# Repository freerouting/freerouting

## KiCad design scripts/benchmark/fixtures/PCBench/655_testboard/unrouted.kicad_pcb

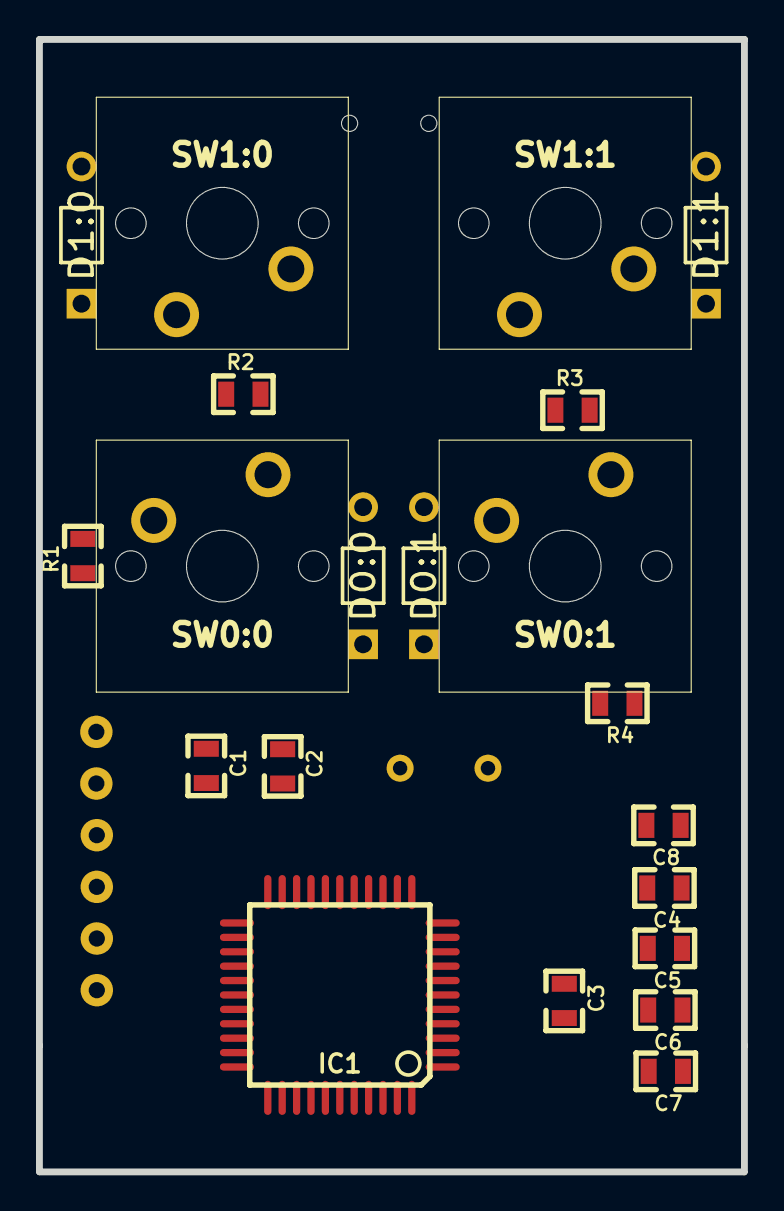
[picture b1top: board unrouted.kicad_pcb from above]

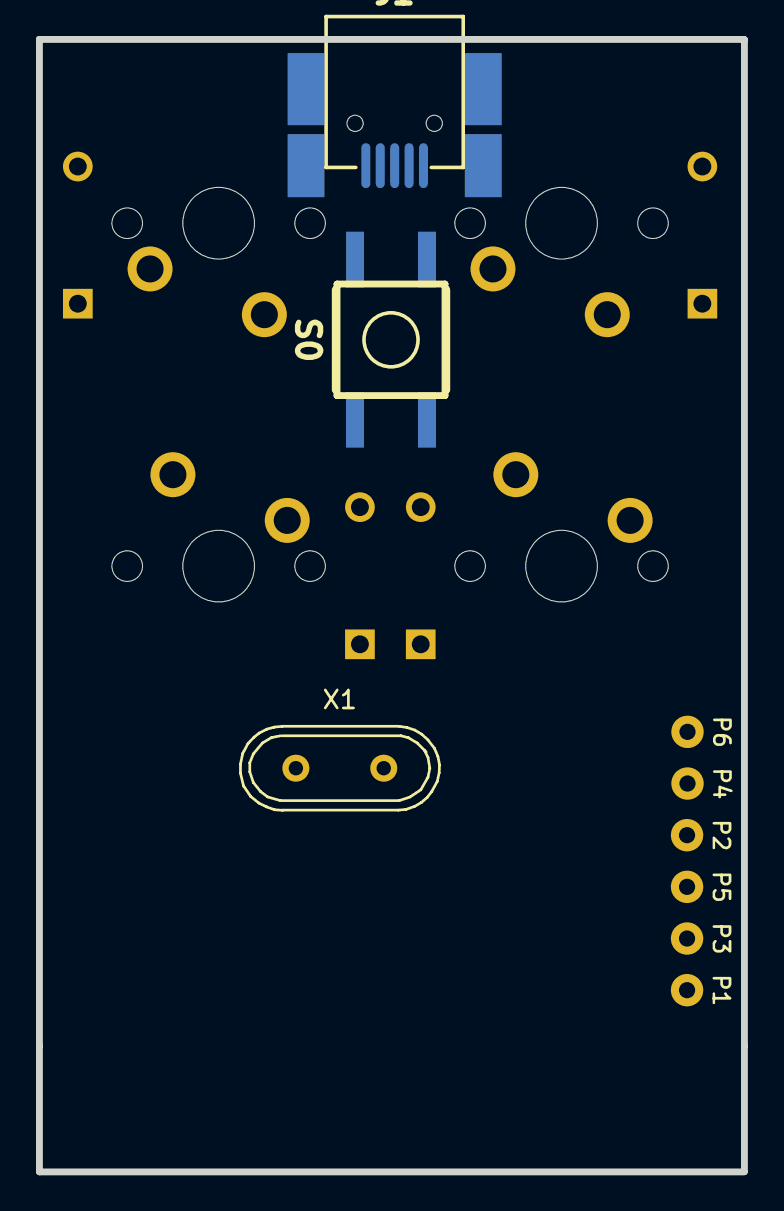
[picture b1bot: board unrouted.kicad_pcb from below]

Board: 2 copper layers, 39.2 x 62.9 mm, 30 parts (9 on the bottom side), 22 nets, no tracks yet.

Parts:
C1, C2: 22p; 0805C
C3, C8: 1u; 0805C
C4, C5, C6, C7: 100n; 0805C
D0:0, D0:1, D1:0, D1:1: D; DIODE
IC1: ATMEGA32U4; TQFP44
J1: USBMINI_B05; 67503
P1, P2, P3, P4, P5, P6: CONN_1; pad
R1, R2: 22; 0805R
R3, R4: 10k; 0805R
S0: DTSM-6; KSEM31GLFS
SW0:0: F0; MX1A
SW0:1: CTRL; MX1A
SW1:0: F1; MX1A
SW1:1: SHIFT; MX1A
X1: CRYSTAL; Crystal_HC49-U_Vertical

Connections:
/COL0: D0:0.2, D1:0.2, IC1.8
/COL1: D0:1.2, D1:1.2, IC1.41
/MISO: IC1.11, P1.1
/MOSI: IC1.10, P4.1
/RES: IC1.13, P5.1, R4.2, S0.3
/ROW0: IC1.18, SW0:0.1, SW0:1.1
/ROW1: IC1.19, SW1:0.1, SW1:1.1
/SCK: IC1.9, P3.1
GND: C1.2, C2.2, C3.2, C4.2, C5.2, C6.2, C7.2, C8.2, IC1.5, IC1.15, IC1.23, IC1.35, IC1.43, J1.5, P6.1, R3.1, S0.1
unnamed: C1.1, IC1.16, X1.1
unnamed: C2.1, IC1.17, X1.2
unnamed: C3.1, IC1.6
unnamed: D0:0.1, SW0:0.2
unnamed: D0:1.1, SW0:1.2
unnamed: D1:0.1, SW1:0.2
unnamed: D1:1.1, SW1:1.2
unnamed: IC1.3, R1.1
unnamed: IC1.4, R2.1
unnamed: IC1.33, R3.2
unnamed: J1.2, R1.2
unnamed: J1.3, R2.2
VCC: C4.1, C5.1, C6.1, C7.1, C8.1, IC1.2, IC1.7, IC1.14, IC1.24, IC1.34, IC1.44, J1.1, P2.1, R4.1

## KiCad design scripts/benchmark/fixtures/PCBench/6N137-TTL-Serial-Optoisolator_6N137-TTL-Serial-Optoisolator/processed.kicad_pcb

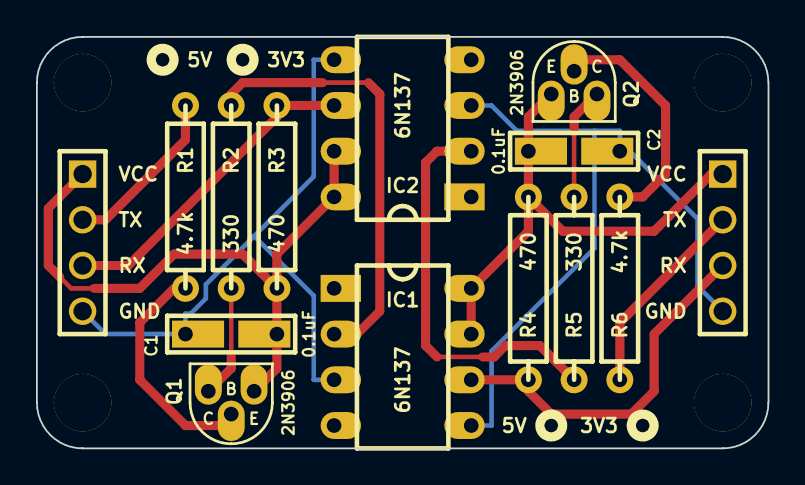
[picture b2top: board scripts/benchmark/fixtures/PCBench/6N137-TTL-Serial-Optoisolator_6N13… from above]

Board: 2 copper layers, 40.6 x 22.9 mm, 18 parts (0 on the bottom side), 14 nets.

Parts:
C1, C2: 0.1uF; CERCAP_2_059B_0805
H***: Val**; hole_M3_2
H***_2, H***_3, H***_4: Val**; hole_M3_2
IC1, IC2: 6N137; DIP8_059Bi_PL
P1, P2: CONN_4; PIN_ARRAY_4x1
Q1, Q2: 2N3906; TO-92_Q_EBC_059Bo_PL
R1, R6: 4.7k; R_AXIAL_0W25_059A_PL
R2, R5: 330; R_AXIAL_0W25_059A_PL
R3, R4: 470; R_AXIAL_0W25_059A_PL

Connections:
GNDA: C1.2, IC1.3, IC2.5, P1.4
GNDB: C2.2, IC1.5, IC2.3, P2.4
unnamed: Q2.2, R6.2
unnamed: Q1.2, R1.2
unnamed: Q1.3, R2.2
unnamed: Q2.3, R5.2
unnamed: IC1.2, R2.1
unnamed: IC2.2, R5.1
RXA: IC2.6, P1.3, R3.1
RXB: IC1.6, P2.3, R4.1
TXA: P1.2, R1.1
TXB: P2.2, R6.1
VCCA: C1.1, IC2.7, IC2.8, P1.1, Q1.1, R3.2
VCCB: C2.1, IC1.7, IC1.8, P2.1, Q2.1, R4.2

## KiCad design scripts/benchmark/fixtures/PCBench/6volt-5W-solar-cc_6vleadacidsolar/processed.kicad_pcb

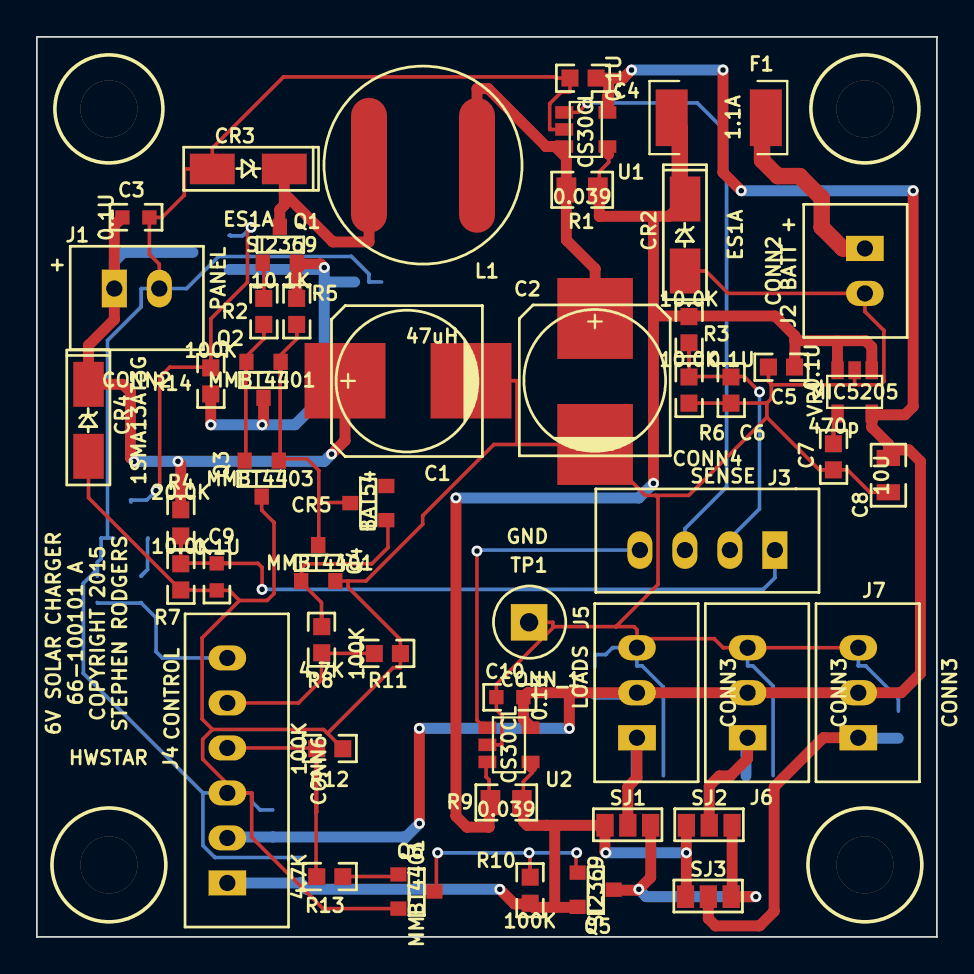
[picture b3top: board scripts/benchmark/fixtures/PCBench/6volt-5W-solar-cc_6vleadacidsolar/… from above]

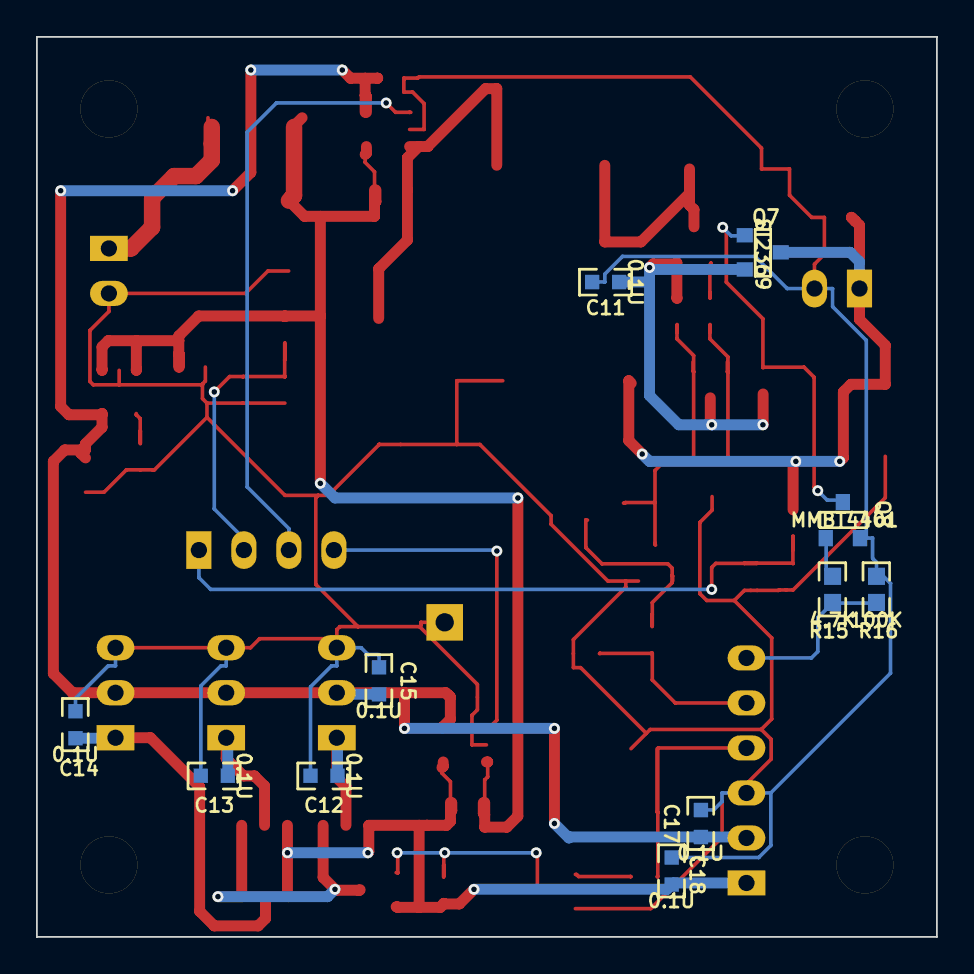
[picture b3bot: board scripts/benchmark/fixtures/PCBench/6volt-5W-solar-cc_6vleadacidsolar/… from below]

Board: 2 copper layers, 50.0 x 50.0 mm, 65 parts (11 on the bottom side), 29 nets.

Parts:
C1, C2: 470U; CAP_ELEC_SMT_8X10
C3, C9, C10, C11, C12, C13, C14, C15, C17, C18: 0.1U; CC0603
C4, C5, C6: 0.1U; RC0603
C7: 470p; RC0603
C8: 10U; CC0805
CR2, CR3: ES1A; SMA-SAR
CR4: 1SMA13AT3G; SMA-SAR
CR5: BAT54; SOT23-3-SAR
F1: 1.1A; MINISMD1812
J1, J2: CONN2; JST_B2B_XH_A
J3: CONN4; JST_B4B_XH_A
J4: CONN6; JST_B6B_XH_A
J5, J6, J7: CONN3; JST_B3B_XH_A
L1: 47uH; BOURNS-SDE0805A
MTGHOLE125, MTGHOLE125_2, MTGHOLE125_3, MTGHOLE125_4: VAL**; MTGHOLE125
Q1, Q5, Q7: SI2369; SOT23-3-SAR
Q2, Q4, Q6, Q8: MMBT4401; SOT23-3-SAR
Q3: MMBT4403; SOT23-3-SAR
R1, R9: 0.039; RC0805
R2: 10; RC0603
R3, R6, R7: 10.0K; RC0603
R4: 20.0K; RC0603
R5: 1K; RC0603
R8, R13, R15: 4.7K; RC0603
R10, R11, R12, R14, R16: 100K; RC0603
SJ1, SJ2, SJ3: GS3; SJ3
TP1: CONN_1; TESTPIN
U1, U2: CS30CL; SOT23-5-SAR
VR1: MIC5205; SOT23-5-SAR

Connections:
+5V: C4.1, C8.1, C10.1, C15.1, C17.1, J4.2, J5.2, J6.2, J7.2, U1.5, U2.5, VR1.5
+BATT: C5.1, CR2.2, F1.1, R1.2, R3.1, R9.1, U1.4, U2.3, VR1.1, VR1.3
/CONVOUT: C2.1, L1.2, R1.1, U1.3
/ICONV: J3.3, U1.1
/ILOAD: J3.4, U2.1
/LOADEN: J4.4, R12.1, R13.1
/PV+: C1.1, C3.1, CR4.2, J1.1, Q7.3, R4.1
/PVEN: J4.6, R15.1, R16.1
/PVSW+: C11.1, Q1.2, Q2.3, Q7.2, R5.1, R14.2
/PWM: J4.5, R8.1, R11.1
/SWCONV: CR3.2, L1.1, Q1.3
/VBATT: C6.1, J3.2, R3.2, R6.1
/VPV: C9.1, J3.1, R4.2, R7.1
/VRAW: C18.1, J4.1, Q5.2, R9.2, R10.1, SJ1.1, SJ2.1, SJ3.1, U2.4
/VRAW1: C12.1, J5.1, SJ1.2
/VRAW2: C13.1, J6.1, SJ2.2
/VRAW3: C14.1, J7.1, SJ3.2
/VRAWSW: Q5.3, SJ1.3, SJ2.3, SJ3.3
GND: C1.2, C2.2, C3.2, C4.2, C5.2, C6.2, C7.2, C8.2, C9.2, C10.2, C11.2, C12.2, C13.2, C14.2, C15.2, C17.2, C18.2, CR2.1, CR3.1, CR4.1, J1.2, J2.2, J4.3, J5.3, J6.3, J7.3, Q3.3, Q4.2, Q6.2, Q8.2, R6.2, R7.2, R11.2, R12.2, R16.2, TP1.1, U1.2, U2.2, VR1.2
unnamed: C7.1, VR1.4
unnamed: CR5.1, Q4.1, R8.2
unnamed: CR5.3, Q2.1, Q3.1, Q4.3, R5.2
unnamed: F1.2, J2.1
unnamed: Q1.1, R2.1
unnamed: Q2.2, Q3.2, R2.2
unnamed: Q5.1, Q6.3, R10.2
unnamed: Q6.1, R13.2
unnamed: Q7.1, Q8.3, R14.1
unnamed: Q8.1, R15.2

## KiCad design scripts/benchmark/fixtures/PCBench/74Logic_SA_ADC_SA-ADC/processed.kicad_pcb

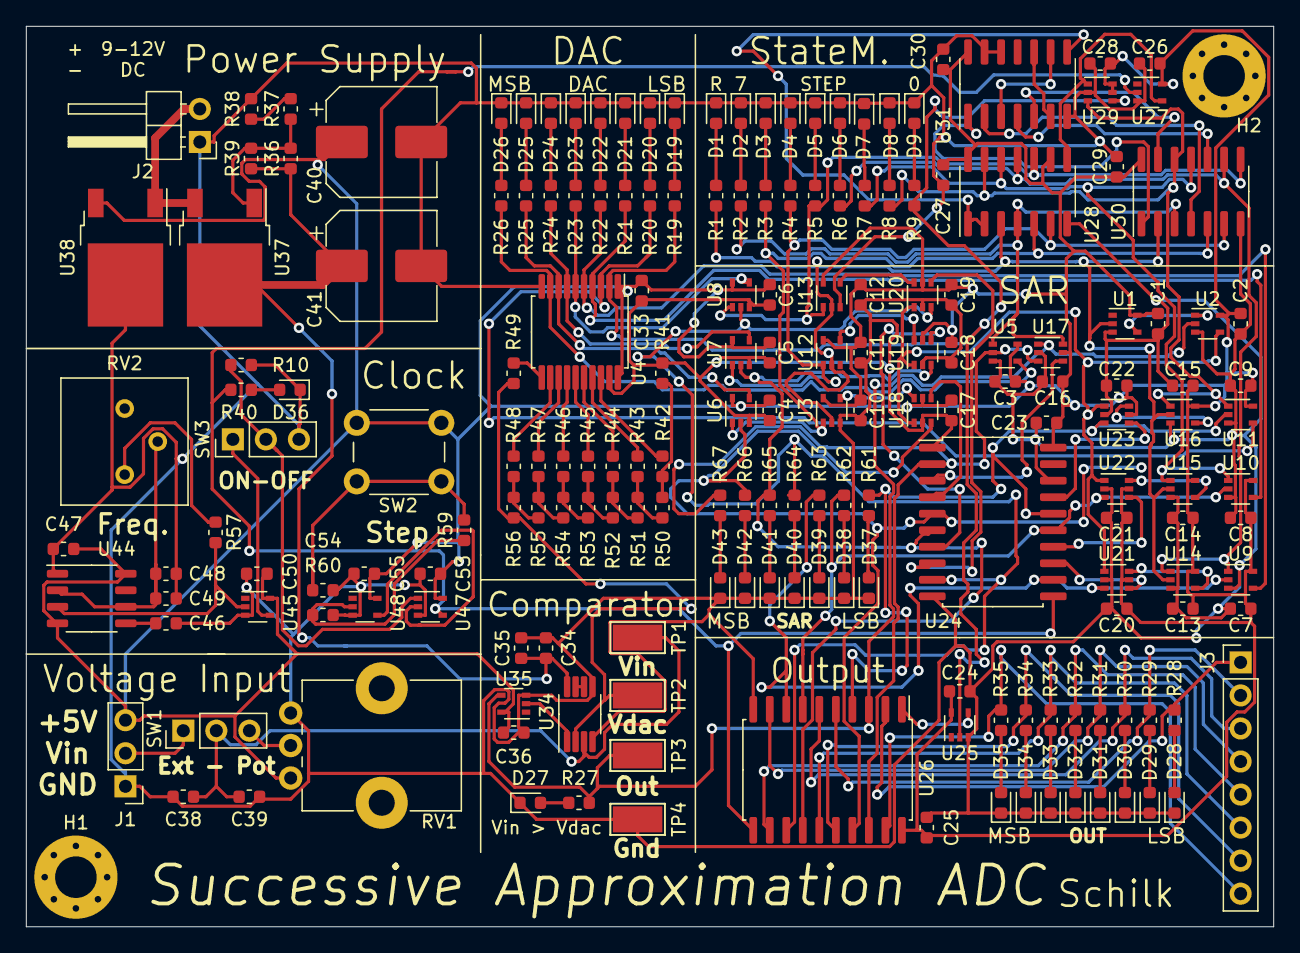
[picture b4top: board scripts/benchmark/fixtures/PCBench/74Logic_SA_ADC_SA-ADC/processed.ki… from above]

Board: 2 copper layers, 95.9 x 69.2 mm, 191 parts (0 on the bottom side), 127 nets.

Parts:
C1, C2, C3, C4, C5, C6, C7, C8, C9, C10, C11, C12, C13, C14, C15, C16, C17, C18, C19, C20, C21, C22, C23, C24, C25, C26, C27, C28, C29, C30, C33, C34, C36, C46, C47, C48, C50, C53, C54, C55: 0u1; C_0603_1608Metric
C35, C38, C39, C49: DNS; C_0603_1608Metric
C40, C41: 100u; CP_Elec_8x6.5
D1, D2, D3, D4, D5, D6, D7, D8, D9, D19, D20, D21, D22, D23, D24, D25, D26, D27, D28, D29, D30, D31, D32, D33, D34, D35, D36, D37, D38, D39, D40, D41, D42, D43: LED; LED_0603_1608Metric
H1, H2: MountingHole; MountingHole_3.2mm_M3_Pad_Via
J1: Vin; PinHeader_1x03_P2.54mm_Vertical
J2: Power; PinHeader_1x02_P2.54mm_Horizontal
J3: Out; PinHeader_1x08_P2.54mm_Vertical
R1, R2, R3, R4, R5, R6, R7, R8, R9, R19, R20, R21, R22, R23, R24, R25, R26, R27, R28, R29, R30, R31, R32, R33, R34, R35, R40, R61, R62, R63, R64, R65, R66, R67: 39K; R_0603_1608Metric
R10, R59, R60: 10K; R_0603_1608Metric
R36: 270R; R_0603_1608Metric
R37: 1K; R_0603_1608Metric
R38: 100R; R_0603_1608Metric
R39: DNS; R_0603_1608Metric
R41, R42, R43, R44, R45, R46, R47, R48, R49: 20K 0.1%; R_0603_1608Metric
R50, R51, R52, R53, R54, R55, R56: 10K 0.1%; R_0603_1608Metric
R57: 5K6; R_0603_1608Metric
RV1: 10K; Potentiometer_Alps_RK09K_Single_Vertical
RV2: 1Meg; Potentiometer_Bourns_3386P_Vertical
SW1, SW3: SW_Push_SPDT; PinHeader_1x03_P2.54mm_Vertical
SW2: SW_Push; SW_PUSH_6mm
TP1: Vin; TestPoint_Keystone_5019_Minature
TP2: Vdac; TestPoint_Keystone_5019_Minature
TP3: CompOut; TestPoint_Keystone_5019_Minature
TP4: GND; TestPoint_Keystone_5019_Minature
U1, U25, U27: SN74LVC1G04DCK; SOT-353_SC-70-5
U2: SN74LVC1G08DCK; SOT-353_SC-70-5
U3, U5, U6, U7, U8, U9, U10, U11, U12, U13, U14, U15, U16, U47: SN74LVC1G32DCK; SOT-353_SC-70-5
U4: SN74HC245DBR; SSOP-20_5.3x7.2mm_P0.65mm
U17, U18, U19, U20, U21, U22, U23: 74LVC1G157GW; SOT-363_SC-70-6
U24, U26: SN74HC377DW; SOIC-20W_7.5x12.8mm_P1.27mm
U28: 74HC161D; SOIC-14_3.9x8.7mm_P1.27mm
U29: SN74LVC1G175DCK; SOT-363_SC-70-6
U30: SN74HC02D; SOIC-14_3.9x8.7mm_P1.27mm
U31: SN74HC08D; SOIC-14_3.9x8.7mm_P1.27mm
U34: LM358ST; MSOP-8_3x3mm_P0.65mm
U35, U45, U48: 74LVC1G17DCK; SOT-353_SC-70-5
U37: LM317; TO-252-2
U38: L7805CDT; TO-252-2
U44: NE555DR; SOP-8_3.9x4.9mm_P1.27mm

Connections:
+5V: C1.1, C2.2, C3.2, C4.2, C5.2, C6.2, C7.2, C8.2, C9.2, C10.2, C11.2, C12.2, C13.2, C14.2, C15.2, C16.2, C17.2, C18.2, C19.2, C20.2, C21.2, C22.2, C23.2, C24.1, C25.2, C26.1, C27.1, C28.1, C29.1, C30.1, C33.2, C36.2, C40.1, C47.2, C50.2, C53.2, C55.2, J1.3, RV1.1, SW2.1, U1.5, U2.5, U3.5, U4.1, U4.20, U5.5, U6.5, U7.5, U8.5, U9.5, U10.5, U11.5, U12.5, U13.5, U14.5, U15.5, U16.5, U17.5, U18.5, U19.5, U20.5, U21.5, U22.5, U23.5, U24.20, U25.5, U26.20, U27.5, U28.9, U28.14, U29.5, U29.6, U30.14, U31.14, U35.5, U38.3, U44.4, U44.8, U45.5, U47.5, U48.5
/Analog/COMP_OUT: R27.2, TP3.1, U2.2, U17.1, U26.3, U35.4
/Analog/D0: R9.2, R19.2, U4.2, U25.2, U29.4
/Analog/D1: R20.2, U4.3, U11.4
/Analog/D2: R21.2, U4.4, U10.4
/Analog/D3: R22.2, U4.5, U9.4
/Analog/D4: R23.2, U4.6, U8.4
/Analog/D5: R24.2, U4.7, U7.4
/Analog/D6: R25.2, U4.8, U6.4
/Analog/D7: R26.2, U4.9, U5.4
/Analog/DAC/D0: R42.2, U4.18
/Analog/DAC/D1: R43.2, U4.17
/Analog/DAC/D2: R44.2, U4.16
/Analog/DAC/D3: R45.2, U4.15
/Analog/DAC/D4: R46.2, U4.14
/Analog/DAC/D5: R47.2, U4.13
/Analog/DAC/D6: R48.2, U4.12
/Analog/DAC/D7: R49.2, U4.11
/Analog/DAC/Vdac: R49.1, R56.1, TP2.1, U34.2
/Clock/CLK: R40.2, U24.11, U26.11, U27.2, U47.4
/Input/VIN: C38.1, C39.1, SW1.2, TP1.1, U34.3
/Output/OUT_1: R61.2, U11.2, U23.3, U24.16, U26.4
/Output/OUT_2: R62.2, U10.2, U22.3, U24.15, U26.7
/Output/OUT_3: R63.2, U9.2, U21.3, U24.12, U26.8
/Output/OUT_4: R64.2, U8.2, U20.3, U24.9, U26.13
/Output/OUT_5: R65.2, U7.2, U19.3, U24.6, U26.14
/Output/OUT_6: R66.2, U6.2, U18.3, U24.5, U26.17
/Output/OUT_7: R67.2, U5.2, U17.3, U24.2, U26.18
/SA-Register.sch/D: U2.4, U18.1, U19.1, U20.1, U21.1, U22.1, U23.1
/SA-Register.sch/STATE1: R8.2, U11.1, U16.1, U28.13, U29.3, U30.12
/SA-Register.sch/STATE2: R7.2, U10.1, U15.1, U28.12, U30.11
/SA-Register.sch/STATE3: R6.2, U9.1, U14.1, U28.11, U30.9
/SA-Register.sch/STATE4: R5.2, U8.1, U13.1, U28.10, U30.8
/SA-Register.sch/STATE5: R4.2, U7.1, U12.1, U28.6, U30.6
/SA-Register.sch/STATE6: R3.2, U3.1, U6.1, U28.5, U30.5
/SA-Register.sch/STATE7: R2.2, U5.1, U17.6, U28.4, U30.3
/SA-Register.sch/STATE_RST: R1.2, U1.2, U3.2, U12.2, U13.2, U14.2, U15.2, U16.2, U28.3, U30.2
/StateMaschine.sch/C_IN: U28.1, U28.2, U31.8
GND: C1.2, C2.1, C3.1, C4.1, C5.1, C6.1, C7.1, C8.1, C9.1, C10.1, C11.1, C12.1, C13.1, C14.1, C15.1, C16.1, C17.1, C18.1, C19.1, C20.1, C21.1, C22.1, C23.1, C24.2, C25.1, C26.2, C27.2, C28.2, C29.2, C30.2, C33.1, C34.2, C35.2, C36.1, C38.2, C39.2, C40.2, C41.2, C46.1, C47.1, C48.1, C49.1, C50.1, C53.1, C54.2, C55.1, D1.1, D2.1, D3.1, D4.1, D5.1, D6.1, D7.1, D8.1, D9.1, D19.1, D20.1, D21.1, D22.1, D23.1, D24.1, D25.1, D26.1, D27.1, D28.1, D29.1, D30.1, D31.1, D32.1, D33.1, D34.1, D35.1, D36.1, D37.1, D38.1, D39.1, D40.1, D41.1, D42.1, D43.1, J1.1, J2.1, R10.1, R38.2, R41.2, R60.2, RV1.3, SW3.3, TP4.1, U1.3, U2.3, U3.3, U4.10, U4.19, U5.3, U6.3, U7.3, U8.3, U9.3, U10.3, U11.3, U13.3, U14.3, U15.3, U16.3, U17.2, U18.2, U19.2, U20.2, U21.2, U22.2, U23.2, U24.1, U24.10, U24.18, U25.3, U26.10, U27.3, U28.7, U29.2, U30.7, U31.7, U31.12, U31.13, U34.4, U34.5, U35.3, U38.2, U44.1, U45.3, U47.3, U48.3
unnamed: C46.2, U44.5
unnamed: C48.2, C49.2, RV2.2, U44.2, U44.6
unnamed: C54.1, R59.1, U48.2
unnamed: D1.2, R1.1
unnamed: D2.2, R2.1
unnamed: D3.2, R3.1
unnamed: D4.2, R4.1
unnamed: D5.2, R5.1
unnamed: D6.2, R6.1
unnamed: D7.2, R7.1
unnamed: D8.2, R8.1
unnamed: D9.2, R9.1
unnamed: D19.2, R19.1
unnamed: D20.2, R20.1
unnamed: D21.2, R21.1
unnamed: D22.2, R22.1
unnamed: D23.2, R23.1
unnamed: D24.2, R24.1
unnamed: D25.2, R25.1
unnamed: D26.2, R26.1
unnamed: D27.2, R27.1
unnamed: D28.2, R28.1
unnamed: D29.2, R29.1
unnamed: D30.2, R30.1
unnamed: D31.2, R31.1
unnamed: D32.2, R32.1
unnamed: D33.2, R33.1
unnamed: D34.2, R34.1
unnamed: D35.2, R35.1
unnamed: D36.2, R40.1
unnamed: D37.2, R61.1
unnamed: D38.2, R62.1
unnamed: D39.2, R63.1
unnamed: D40.2, R64.1
unnamed: D41.2, R65.1
unnamed: D42.2, R66.1
unnamed: D43.2, R67.1
unnamed: J1.2, SW1.1
unnamed: J2.2, U37.3, U38.1
unnamed: J3.1, R28.2, U26.2
unnamed: J3.2, R29.2, U26.5
unnamed: J3.3, R30.2, U26.6
unnamed: J3.4, R31.2, U26.9
unnamed: J3.5, R32.2, U26.12
unnamed: J3.6, R33.2, U26.15
unnamed: J3.7, R34.2, U26.16
unnamed: J3.8, R35.2, U26.19
unnamed: R10.2, SW3.2, U47.1
unnamed: R36.2, R37.1, R39.2, U37.1
unnamed: R37.2, R38.1
unnamed: R41.1, R42.1, R50.1
unnamed: R43.1, R50.2, R51.2
unnamed: R44.1, R51.1, R52.2
unnamed: R45.1, R52.1, R53.2
unnamed: R46.1, R53.1, R54.2
unnamed: R47.1, R54.1, R55.2
unnamed: R48.1, R55.1, R56.2
unnamed: R57.1, RV2.1
unnamed: R57.2, U44.3, U45.2
unnamed: R59.2, R60.1, SW2.2
unnamed: RV1.2, SW1.3
unnamed: SW3.1, U45.4
unnamed: U1.4, U2.1
unnamed: U12.4, U19.6
unnamed: U13.4, U20.6
unnamed: U14.4, U21.6
unnamed: U15.4, U22.6
unnamed: U16.4, U23.6
unnamed: U17.4, U24.3
unnamed: U18.4, U24.4
unnamed: U3.4, U18.6
unnamed: U19.4, U24.7
unnamed: U20.4, U24.8
unnamed: U21.4, U24.13
unnamed: U22.4, U24.14
unnamed: U23.4, U24.17
unnamed: U25.4, U26.1
unnamed: U27.4, U28.8, U29.1
unnamed: U30.1, U31.1
unnamed: U30.4, U31.2
unnamed: U30.10, U31.4
unnamed: U30.13, U31.5
unnamed: U31.3, U31.9
unnamed: U31.6, U31.10
unnamed: U34.1, U35.2
unnamed: U34.6, U34.7
unnamed: U47.2, U48.4
VDDA: C34.1, C35.1, C41.1, R36.1, R39.1, U34.8, U37.2

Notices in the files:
scripts/benchmark/fixtures/PCBench/6volt-5W-solar-cc_6vleadacidsolar/processed.kicad_pcb:
COPYRIGHT 2015
